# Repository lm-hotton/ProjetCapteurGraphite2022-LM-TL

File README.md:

# ProjetCapteurGraphite2022-LM-TL
***
## Sommaire
1. [Description du projet, objectifs et livrables](https://github.com/lm-hotton/ProjetCapteurGraphite2022-LM-TL/blob/LM#1-description-du-projet-objectifs-et-livrables)
2. [Jauge de Déformation à base de graphite](https://github.com/lm-hotton/ProjetCapteurGraphite2022-LM-TL/blob/LM#2-jauge-de-d%C3%A9formation-%C3%A0-base-de-graphite)
3. [PCB Shield](https://github.com/lm-hotton/ProjetCapteurGraphite2022-LM-TL/blob/LM#3-pcb-shield)
- 3.1. Choix du circuit amplificateur transimpédance
- 3.2. Test circuit électrique sur LTSpice
- 3.3. Réalisation d'un PCB (KiCad)
- 3.4. Fabrication du SHIELD
- 3.4.1. Fabrication du PCB
- 3.4.2. Perçage et soudure
4. [Code Arduino](https://github.com/lm-hotton/ProjetCapteurGraphite2022-LM-TL/blob/LM#4-code-arduino)
5. [APK Arduino](https://github.com/lm-hotton/ProjetCapteurGraphite2022-LM-TL/blob/LM#5-apk-android)
6. [Banc de test](https://github.com/lm-hotton/ProjetCapteurGraphite2022-LM-TL/blob/LM#6-banc-de-test)
7. [Datasheet](https://github.com/lm-hotton/ProjetCapteurGraphite2022-LM-TL/blob/LM#7-datasheet)
8. [Solutions d'amélioration](https://github.com/lm-hotton/ProjetCapteurGraphite2022-LM-TL/blob/LM#8-solutions-dam%C3%A9lioration)

***
## 1. Description du projet, objectifs et livrables

### 1.1. Description du projet et objectifs
Ce projet est inscrit dans le cadre de l'UF "Du capteur au banc de test en open source hardware". Il est basée sur les travaux de chercheurs dans le domaine des capteurs afin d’évaluer les potentialités de leur technologie low-tech. Cette année, le capteur étudié est un [capteur de déformation à base de graphite](https://www.researchgate.net/publication/259846610_Pencil_Drawn_Strain_Gauges_and_Chemiresistors_on_Paper). 
Pour réaliser ce projet, il faut comprendre les propriétés physiques du capteur, concevoir et réaliser un système d'acquisition, élaborer un banc de test pour notre capteur pour enfin rédiger la datasheet de ce capteur.
### 1.2. Livrables
Les livrables de ce projet sont donc: 
- un **shield PCB** associé à une carte Arduino UNO comprenant:
  - **un circuit analogique amplificateur transimpédance**
  - **un module bluetooth** permettant de transmettre les mesures sur un téléphone
  - un écran OLED permettant de voir les mesures en temps réel
  - un encodeur rotatif permettant de naviguer dans le menu de l'écran OLED
- le **code Arduino** permettant:
  - la mesure de notre capteur de déformation à base de graphite
  - d'envoyer les données via un module bluetooth
  - l'affichage sur un écran OLED
  - l'encodeur rotatif permettant de naviguer dans le menu de l'OLED

Nous avons également créé un **APK Android** permettant d'afficher la valeur de la résistance mesurée sur un smartphone.

Enfin nous avons conçu un **banc de test** pour notre capteur afin de rédiger une **datasheet** associée et pouvoir proposer des **solutions d'améliorations et les limites** pour ce type de capteur.
***

## 2. Jauge de déformation à base de graphite
Les dispositifs électroniques à base de papier sont de plus en plus étudiés pour des applications comme des antennes, des circuits imprimés, des capteurs... En effet ils sont:
- flexibles
- fins
- peu chers
- portables
- écologiques

Quand on trace un trait au crayon sur du papier, la friction entre le crayon et le papier arrache des particules de graphite qui adhèrent sur les fibres de papier. Ainsi les crayons à papier sont un bon moyen de déposer de fines particules de graphite sur un support.
Ces traces de crayon peuvent être vues comme de fins films conducteurs fait de réseaus de particules de graphite.

Les différents types de crayon à papier varie en fonction de la composition de leurs mines. Les mines vont du 9H, les plus durs, jusqu'au 9B, les moins dur. Plus les mines sont dures, moins il y a de carbone dans leur composition, moins le film de graphite qu'elles déposent est conducteur.
Ainsi, le 9B est plus conducteur que le 9H.
Dans notre projet, nous avons utilisé des crayons **HB et B**.

Le principe physique du capteur repose sur l'organisation en **système granulaire** du réseau des nanoparticules de graphite sur le papier.

En effet, la **conductance d'un système granulaire** varie en fonction :
- des **distances internanoparticules**
- de la constante de l'effet tunnel
- de l'énergie de charge de Coulomb
- de la température

Ici, la compression et l'extension de la feuille de papier peut modifier la distance entre les Nano particules de graphite. La compression rapproche les particules de graphite, augmente la conductance, diminue la résistivité. Au contraire, l'extension de la feuille de papier Augmente la distance entre les particules de graphite, diminue la conductance, augmente la résistance.
Ainsi, en mesurant la variation de la résistance entre les deux électrodes de notre capteur, nous pouvons en déduire la déformation de notre capteur.

***
## 3. PCB shield
### 3.1. Choix du circuit amplificateur transimpédance
Dans notre projet, nous souhaitons mesurer la résistance de notre capteur.
Nous décidons d'imposer une tension au borne de notre capteur et de mesurer le courant pour en déduire la résistance. 
Cependant le courant que nous devons mesurer est très faible du nano au micro-ampère.
Or notre microcontroleur Arduino Uno possède les caractéristiques suivantes:
- résolution 10 à 12 bits (1024 à 4096 points)
- pleine échelle (VRef) de 1.1 V à 5.0 V
- impédance de source max 1 kOhm à 10 kOhm
- fréquence d'échantillonnage max de l'ordre du MHz

La mesure directe d'un courant aussi faible que celui que fourni notre capteur ne parait pas possible.

Nous choisissons d'utiliser la solution d'un amplificateur transimpédance:

Cette solution permet :
- la conversion courant I -> tension U dans la résistance d'épreuve R1 (shunt)
- l' amplification à fort gain par montage non-inverseur
- la chute de tension sur R1 perturbe (un peu) la tension appliquée au capteur
- peut fonctionner avec seulement une alimentation positive (nécessaire avec l'utilisation d'un microcontroleur Arduino Uno)

Gain de l’étage de l’AOP : (R2+R3)/R2=(1k+500k)/1k=501

Tension aux bornes de R1 : le courant Isens est d’environ 100nA 
 -> V = 100kOhm*100nA=10-2V=10mV

 Tension sur l’ADC : Gain*Tension aux bornes de R1 => 501*10x10-3~5V 

Nous devons donc choisir un amplificateur possèdant les caractéristiques suivantes :
- un **faible courant d'entrée**: doit être très petit devant Isens pour avoir le Isens traverse la résistance R1 et
pas l’entrée 
- un **ultra-faible offset de tension** : c'est une erreur constante aux entrées de l’amplificateur différentiel dû à un
état non compensé sur l’étage d’entrée de l’amplificateur. On veut que cet offset soit
négligeable devant la tension mesurée sur R1 qui sera de 10mV. 
- **doit supporter un mode commun à la tension d'alimentation négative** ("low rail") : tension commune aux deux entrées, un bon amplifieur sera insensible
à ce mode commun. Si le Isens =0A ,on veut 0V sur l’ADC. LTC1050C => 5µV offset
voltage, et maximum offset voltage drift : 0.05µV/°C. Bien comparé aux 10mV aux
bornes de R1. 

L'[amplificateur opérationel LTC1050C](https://github.com/lm-hotton/ProjetCapteurGraphite2022-LM-TL/blob/main/Datasheet_LTC1050/Datasheet_LTC1050.pdf) satisfait bien toutes ces contraintes.

**Filtrage:**

Cependant un montage aussi sensible étant vulnérable au bruit à 50Hz (+ harmoniques) résultant du couplage capacitif avec le réseau 230V, un **filtrage passe-bas est indispensable**.
D'autres sources de bruit à filtrer sont les horloges de circuits digitaux (microcontrôleur, afficheurs, etc...) et les transceivers RF (bluetooth, etc...). Ce filtrage peut être effectué en partie du coté digital, par programme, sur le microcontrôleur. Cependant un **filtrage analogique est indispensable**, en effet un excès de bruit à l'entrée de l'ADC pourrait amener celui-ci à saturation. 

Nous décidons de filtrer dans 3 régions de la chaîne de traitement analogique :
- **filtre passif à l'entrée** : permet d'éviter que les bruits HF causent de la distorsion dans les étages d'entrée
- **filtre actif basé sur les amplificateurs opérationnels** : maximum d'efficacité
- **filtre passif en fin de chaine**, coté ADC, pour retirer le bruit introduit en cours de traitement (bruit d'alimentation, bruit d'horloge des amplificateurs à découpage)

- **R5** en entrée protège l'ampli opérationnel contre les décharges électrostatiques, en forme avec C1 un filtre pour les bruits en tension
- **C1 avec R1** forme un **filtre pour le bruit en courant**
- **C4 avec R3** forme un **filtre actif**
- **C2 avec R6** forme le **filtre de sortie**
- **C3** filtre le bruit d'alimentation 

Nous allons maintenant tester ce circuit à l'aide du logiciel d'électronique analogique LTSpice.

### 3.2. Test circuit électrique sur LTSpice
Nous réalisons un schéma de notre circuit d'amplification transimpédance sur LTSpice pour simuler son comportement.

#### Test fonctionalité dans les conditions nominales

Dans les conditions nominales, nous obtenons bien un gain de 100 en sortie du circuit amplificateur.

Vérification de la tension de sortie avec un pulse de courant d'entrée à 100 nA.
#### Incidence de l'offset de l'amplificateur
La [datasheet de l'amplificateur opérationel LTC1050C](https://github.com/lm-hotton/ProjetCapteurGraphite2022-LM-TL/blob/main/Datasheet_LTC1050/Datasheet_LTC1050.pdf)
nous indique que l'offset de tension en sortie de l'amplificateur est de 5uV. On veut que cet offset soit
négligeable devant la tension mesurée sur R1 qui sera de 10mV. 
L'incidence de l'offset de cet amplificateur est donc acceptable.
#### Incidence du courant d'entrée de l'amplificateur
La [datasheet de l'amplificateur opérationel LTC1050C](https://github.com/lm-hotton/ProjetCapteurGraphite2022-LM-TL/blob/main/Datasheet_LTC1050/Datasheet_LTC1050.pdf)
nous indique que l'offset de courant en entrée de l'amplificateur est de +/- 200 pA, bien inférieur à 100nA. 
On a donc un faible courant d'entrée, très petit devant Isens pour avoir le Isens qui traverse la résistance R1 et
pas l’entrée de l'amplificatieur.
L'incidence de l'offset de cet amplificateur est donc acceptable.
#### Fréquence de coupure de chaque étage de filtre passe-bas
##### Etage C1-R1: Filtre pour le bruit en courant

- fc = 16 Hz
##### Etage C4-R3: Filtre actif

- fc = 1,6 Hz
##### Etage C2-R6: Filtre de sortie

- fc = 1,6 kHz
#### Atténaution globale d'un bruit en courant à la fréquence de limite de repliement dans le cas de l'ADC Arduino UNO

On constate qu'il y a une atténuation d'un bruit en courant environ égale à **40dB pour une fréquence autour de 50Hz** et de **100 dB pour un bruit en courant au voisinage de la fréquence de repliement de spectre** (7,7 kHz).
#### Expression analytique de la résistance du capteur en fonction des éléments du circuit transimpédance
R1 = 100 000 Ohm
R2 = 1000 Ohm
R3 = 100 000 Ohm
R4 = 10 000 Ohm
Vcc = 5 V

-> Rsens (Ohm) = (1+R3/R2).R1.(Vcc/(Vadc.5/1024))-R1-R4

### 3.3. Réalisation d'un PCB (KiCad)
Pour réaliser les schématiques et les empreintes de de nos composants, nous nous servons de leurs [datasheets](https://github.com/lm-hotton/ProjetCapteurGraphite2022-LM-TL/blob/main/Datasheets_Compsants) en ligne. 
Pour faire le PCB, nous avons respecté quelques règles :
- Largeur de piste: 0.6 mm minimum,
- Isolation de piste : 0.9mm minimum
- Bluetooth, Encodeur rotatif, OLED, Connecteurs (header): pad à 1mm de percage, Ovale 2*2.54mm
- Résistance, Capacité, Support d'AOP: Pad à 0.8mm de percage, Cercle 2.54mm
- Support de l'AOP: pad n°1 rectangulaire, les autres sont ovales ou ronds

#### Schematique et empreinte de l'OLED
 
#### Schematique et empreinte du module bluetooth HC-O5
 
#### Schematique et empreinte de l'encodeur rotatif KY-040
 
#### Schematique et empreinte l'amplificateur opérationel LTC1050
 
#### Schematique et empreinte des pins de la carte Arduino

#### Schematique du circuit amplificateur transimpédance

#### Empreinte du PCB complet
Nous avons utilisé l'empreinte d'une carte Arduino Uno existante dans les bibliothèques de KiCad, sur laquelle nous avons placé nos composants. 
Les masses (GND) sont toutes reliées entre elles par une piscine ce qui permet une meilleure homogénéité des équipotentiels sur tout le circuit, pour de meilleurs résultats à haute fréquence.
Il faut faire attention de ne par dessiner de pistes avec des angles droits pour éviter d'éventuels problèmes lors de la fabrication du PCB. 

Enfin, nous avons soudé chaque composant à l'aide d'un fer à souder.

#### **Visualisation 3D du PCB entier**

### 3.4. Fabrication du SHIELD
#### 3.4.1. Fabrication du PCB
Le PCB est fabriqué sur une plaquette recouverte d'une fine couche de cuivre, elle même recouverte d'une couche de résine photosensible aux UV.
Nous avons tout d'abord imprimé notre modélisation du circuit sur un film plastique qui nous sert de calque. 

Une insolation sous UV pendant 2 minutes permet de transposer ce calque sur notre couche de résine, permettant ainsi d'enlever la partie de la résine insolée.
Ensuite, la plaquette a été déposée dans un bain de perchlorure de fer afin d'être gravée (environ 8 minutes). Seule la partie du cuivre non protégée par la résine est décapée.
Pour finir, de l'acétone a été appliquée sur la plaquette pour éliminer les dernières traces de résine.
## 3.4.2. Perçage et soudure
Une fois le circuit en cuivre du PCB réalisé, nous avons percé les trous sur notre plaquette à l'aide d'une perçeuse électrique. 
***
## 4. Code Arduino
Voici le code arduino qui permet d'acquérir les mesures de notre capteur, les afficher sur l'écran OLED et les envoyer par bluetooth à un smatrphone.
```
//code Capteur
int flexPin=A0;

//code bluetooth
#include <SoftwareSerial.h>
#define rxPin 11
#define txPin 10
#define baudrate 9600
SoftwareSerial mySerial(rxPin, txPin);

//code OLED
#include <Adafruit_SSD1306.h>
#define nombreDePixelsEnLargeur 128         // Taille de l'écran OLED, en pixel, au niveau de sa largeur
#define nombreDePixelsEnHauteur 64          // Taille de l'écran OLED, en pixel, au niveau de sa hauteur
#define brocheResetOLED         -1          // Reset de l'OLED partagé avec l'Arduino (d'où la valeur à -1, et non un numéro de pin)
#define adresseI2CecranOLED     0x3C        // Adresse de "mon" écran OLED sur le bus i2c (généralement égal à 0x3C ou 0x3D)
Adafruit_SSD1306 ecranOLED(nombreDePixelsEnLargeur, nombreDePixelsEnHauteur, &Wire, brocheResetOLED);

//code encodeur
int encoderPinA = 2; // CLK pin
int encoderPinB = 3; // DT pin
int encoderBtn = 4; // SW pin
int count = 0;
int encoderPinA_prev;
int encoderPinA_value;
boolean bool_CW;

void setup() {

  //code bluetooth
  pinMode (rxPin, INPUT);
  pinMode (txPin, OUTPUT);
  Serial.begin(baudrate);
  mySerial.begin(baudrate);

  //code capteur
  pinMode(flexPin,INPUT);

  //code Encodeur
  pinMode (encoderPinA, INPUT);
  pinMode (encoderPinB, INPUT);
  pinMode(encoderBtn, INPUT_PULLUP);
  encoderPinA_prev = digitalRead(encoderPinA);

  //code OLED
  if(!ecranOLED.begin(SSD1306_SWITCHCAPVCC, adresseI2CecranOLED))
    while(1);                               // Arrêt du programme (boucle infinie) si échec d'initialisation

   ecranOLED.clearDisplay();
   ecranOLED.setCursor(0, 0);
   ecranOLED.setTextColor(SSD1306_WHITE);
   ecranOLED.setTextSize(2);
}

void loop() {

  //code capteur
  float ADCflex=analogRead(flexPin);
  //Serial.println(String(ADCflex));
  //Serial.println();
  
  float Volt=(ADCflex*5/1023);
  //Serial.println(String(Volt));
  //Serial.println();
 
  float Res=((1+100000/1000)*100000*(5/Volt)-100000-10000)/1000000;
  Serial.println(String(Res));
  //Serial.println();

  // code bluetooth
  mySerial.print(Res);

   // OLED
   ecranOLED.setCursor(0, 0);
   ecranOLED.print(Volt);
   ecranOLED.print(" V \n");
   ecranOLED.print(Res);
   ecranOLED.print(" MOhm \n");
   ecranOLED.display();                            // Transfert le buffer à l'écran
   delay(1000);
   ecranOLED.clearDisplay();
}
```
***
## 5. APK Android

***
## 6. Banc de test
Nous avons élaborer un banc de test à l'aide d'un servomoteur, du scotch double face et des morceaux de carton et plastique d'empballage. 
Une partie du capteur est fixée sur le stator à l'aide d'un morceau de carton et d'un scotch double face, et l'autre partie du capteur est maitenue dans l'axe du rotor à l'aide d'un morceau de plastique et de scotch double face.

### Premier test : DeltaR/R0 HB Compression
Pour réaliser cette partie, nous avons mesurer 5 cycles de compression que nous avons moyenner pour obtenir la variation de résistance relative en fonction de l'angle appliqué entre les deux extrémités du capteur.

### Second test : DeltaR/R0 HB Extension
Pour réaliser cette partie, nous avons mesurer 5 cycles d'extension que nous avons moyenner pour obtenir la variation de résistance relative en fonction de l'angle appliqué entre les deux extrémités du capteur.

### Troisième test : DeltaR/R0 B Compression
Pour réaliser cette partie, nous avons mesurer 5 cycles de compression que nous avons moyenner pour obtenir variation de la résistance relative en fonction de l'angle appliqué entre les deux extrémités du capteur.

### Quatrième test : DeltaR/R0 B Extension
Pour réaliser cette partie, nous avons mesurer 5 cycles d'extension que nous avons moyenner pour obtenir la variation de résistance relative en fonction de l'angle appliqué entre les deux extrémités du capteur.

### Cinquième test : Répetabilité des mesures HB
Pour réaliser cette partie, nous effectuons plusieurs cycles de compression-déflexion jusqu'à obtenir des valeurs divergentes des premières de plus de 10%.

Nous pouvons voir qu'à partir de à peu près 260 cycles, le capteur ne peut plus garantir de bons résultats en deflexion.
Les mesures en compression restent valables au dela.

### Sixième test : Répetabilité des mesures B
Pour réaliser cette partie, nous effectuons plusieurs cycles de compression-déflexion jusqu'à obtenir des valeurs divergentes des premières de plus de 10%.

Nous pouvons voir qu'à partir d'une centaine de cycles, le capteur ne peut plus garantir de bons résultats en deflexion.
Les mesures en compression restent valables au dela.

***
## 7. Datasheet
Voici la [datasheet](https://github.com/lm-hotton/ProjetCapteurGraphite2022-LM-TL/blob/main/Datasheet_CapteurGraphite/Datasheet_CapteurGraphite.pdf) de notre capteur.
***
## 8. Solutions d'amélioration
### Solutions d'amélioration
- Trouver une méthode pour déposer la même quantité de graphite sur chaque capteur testé
- Anticiper les besoins du banc de test dans la conception du PCB
- Trouver un moyen de fixer les pinces sur les electrodes lors des mesures
***

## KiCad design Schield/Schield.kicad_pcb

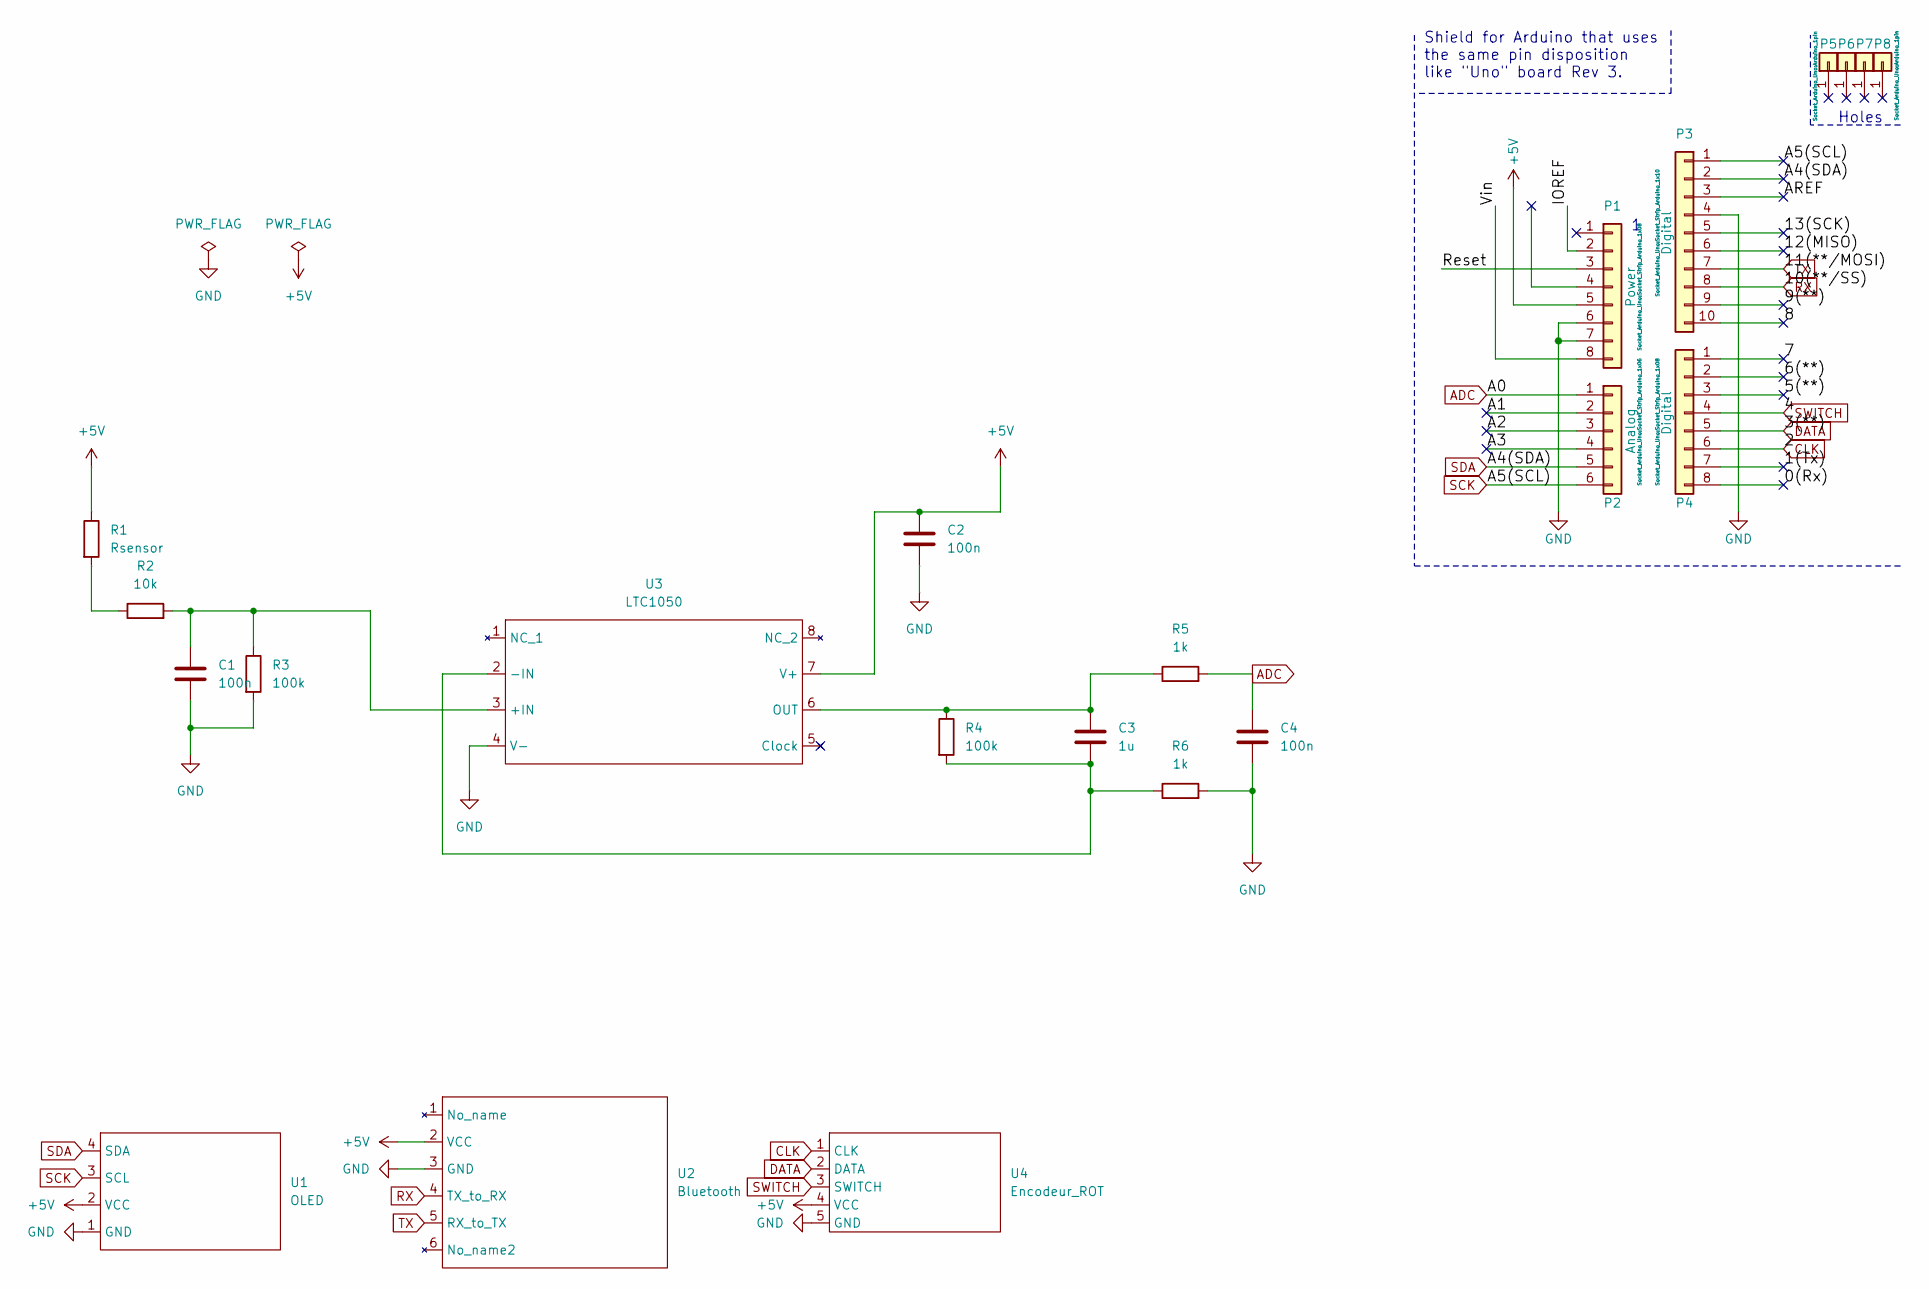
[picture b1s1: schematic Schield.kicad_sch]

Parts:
C1, C2, C4: 100n; C_Disc_D7.5mm_W5.0mm_P5.00mm
C3: 1u; C_Disc_D7.5mm_W5.0mm_P5.00mm
P1: Power; Socket_Strip_Arduino_1x08
P2: Analog; Socket_Strip_Arduino_1x06
P3: Digital; Socket_Strip_Arduino_1x10
P4: Digital; Socket_Strip_Arduino_1x08
P5, P6, P7, P8: CONN_01X01; Arduino_1pin
R1: Rsensor; R_Axial_DIN0204_L3.6mm_D1.6mm_P7.62mm_Horizontal
R2: 10k; R_Axial_DIN0204_L3.6mm_D1.6mm_P7.62mm_Horizontal
R3, R4: 100k; R_Axial_DIN0204_L3.6mm_D1.6mm_P7.62mm_Horizontal
R5, R6: 1k; R_Axial_DIN0204_L3.6mm_D1.6mm_P7.62mm_Horizontal
U1: OLED
U2: Bluetooth
U3: LTC1050
U4: Encodeur_ROT

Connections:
+5V: C2.1, P1.5, R1.1, U1.2 (VCC), U2.2 (VCC), U3.7 (V+), U4.4 (VCC)
/0(Rx): P4.8
/1(Tx): P4.7
/5(**): P4.3
/6(**): P4.2
/7: P4.1
/8: P3.10
/9(**): P3.9
/12(MISO): P3.6
/13(SCK): P3.5
/A1: P2.2
/A2: P2.3
/A3: P2.4
/AREF: P3.3
/IOREF: P1.2
/Reset: P1.3
/Vin: P1.8
ADC: C4.1, P2.1, R5.2
CLK: P4.6, U4.1 (CLK)
DATA: P4.5, U4.2 (DATA)
GND: C1.2, C2.2, C4.2, P1.6, P1.7, P3.4, R3.2, R6.2, U1.1 (GND), U2.3 (GND), U3.4 (V-), U4.5 (GND)
unnamed: C1.1, R2.2, R3.1, U3.3 (+IN)
unnamed: C3.1, R4.1, R5.1, U3.6 (OUT)
unnamed: C3.2, R4.2, R6.1, U3.2 (-IN)
unnamed: R1.2, R2.1
RX: P3.8, U2.4 (TX_to_RX)
SCK: P2.6, P3.1, U1.3 (SCL)
SDA: P2.5, P3.2, U1.4 (SDA)
SWITCH: P4.4, U4.3 (SWITCH)
TX: P3.7, U2.5 (RX_to_TX)

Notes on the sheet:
Holes
Shield for Arduino that uses the same pin disposition like "Uno" board Rev 3.

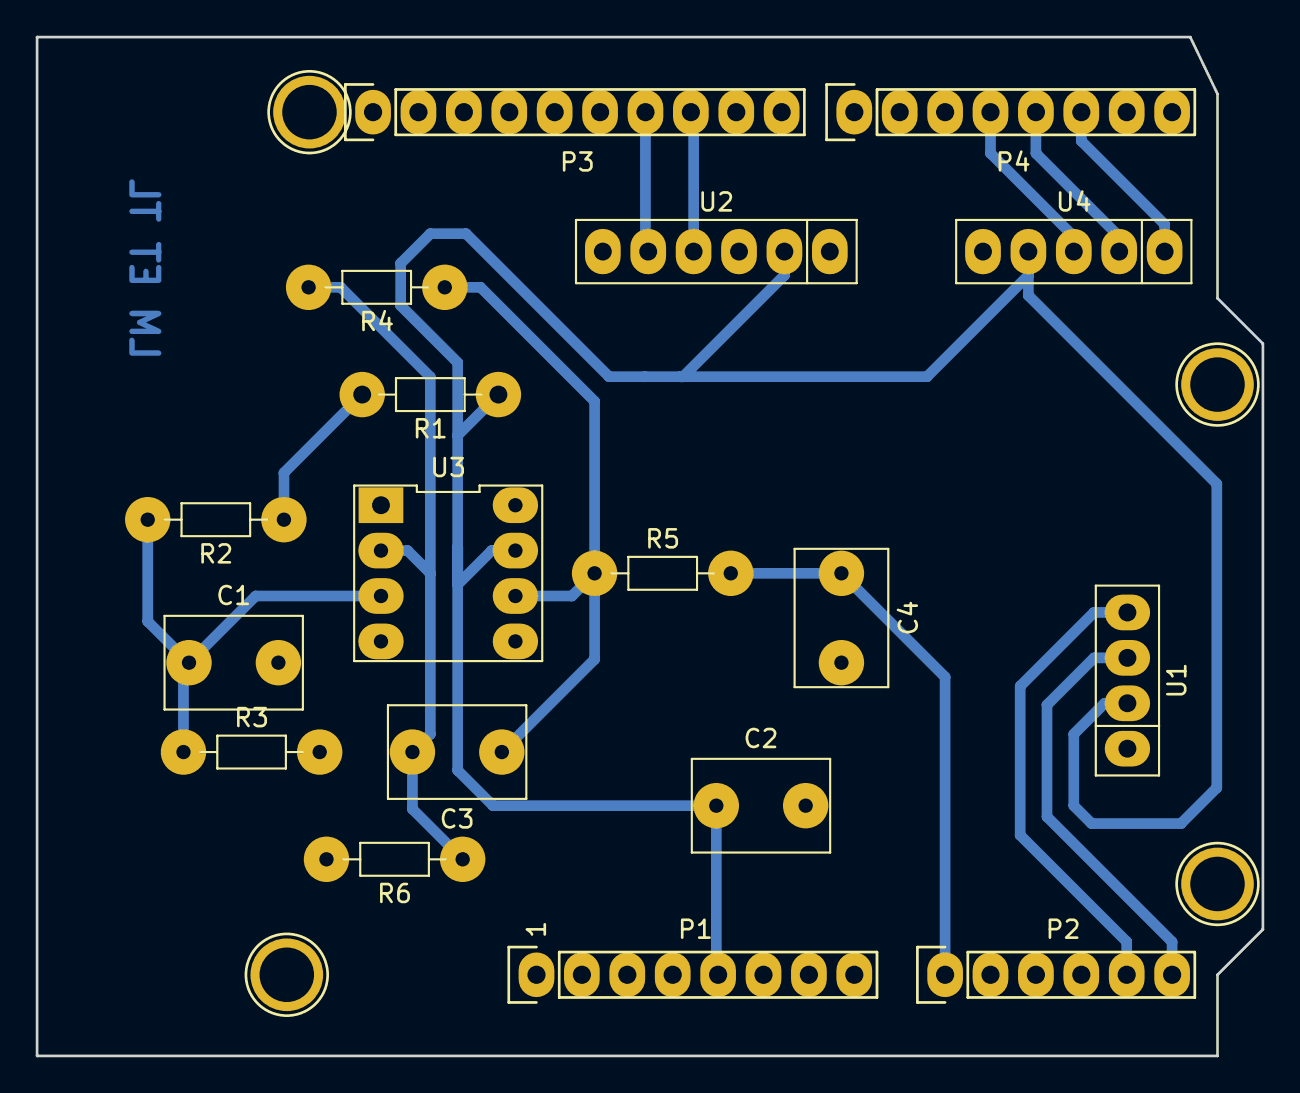
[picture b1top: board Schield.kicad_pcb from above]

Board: 2 copper layers, 68.6 x 57.0 mm, 22 parts (0 on the bottom side), 14 nets.

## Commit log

2022-04-09 Ajout du dossier KiCad
2022-04-10 First update README.md
    Plan du README
2022-04-10 Rédaction de la partie description du READLE.md
2022-04-10 Première version de la partie PCB + Sommaire
2022-04-10 Ajout photos circuit analogique
2022-04-10 Test image
2022-04-10 Changement noms des photos (sans espace)
2022-04-10 Changement du chemin de l'image (mettre le chemin URL)
2022-04-10 2ème version partie PCB
2022-04-10 PREMIERE VERSION
2022-04-12 Ajout des plans 3D du banc de test
2022-04-12 Mise à jour README + Photo kicad + PDF moteur Servo
2022-04-12 Changement tailles Photos
2022-04-12 Test ajout code ARDUINO
2022-04-13 Ajout photos LTSpice + Création dossier pour les photos Kicad
2022-04-14 mise à jour README avec code arduino
2022-04-14 Résolution pb image readme
2022-04-14 changement adresses photos après le merge
2022-04-16 Transfert Ordi Insa
2022-04-16 Photos Résultats Test
2022-04-16 Ajout photos résultats au readme
2022-04-16 Ajout APK
2022-04-17 Review README jusqu'à LTSPICE
2022-04-17 Ajout Photos LTSpice
2022-04-17 Ajout video Banc
2022-04-17 Modification graph %
2022-04-18 datasheet
